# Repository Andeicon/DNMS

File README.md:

# Digital Noice Meter, Particular Matter, Humidity, Air Pressure & Temperature sensor
### based/forked on the great work of Helmut Bitters DNMS (https://github.com/hbitter/DNMS)

This PCB is based on the DNMS-T4.0+NodeMCU Bord of H.Bitters project changed for my own designed 3d Printed case.

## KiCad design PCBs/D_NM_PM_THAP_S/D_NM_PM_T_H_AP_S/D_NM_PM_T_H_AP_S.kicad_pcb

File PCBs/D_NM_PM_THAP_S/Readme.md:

# Digital Noice Meter, Particular Matter, Humidity, Air Pressure & Temperature sensor
## based/forked on the great work of Helmut Bitters DNMS (https://github.com/hbitter/DNMS)

This PCB is based on the DNMS-T4.0+NodeMCU Bord of H.Bitters project changed for my own disgned 3d Printed case.

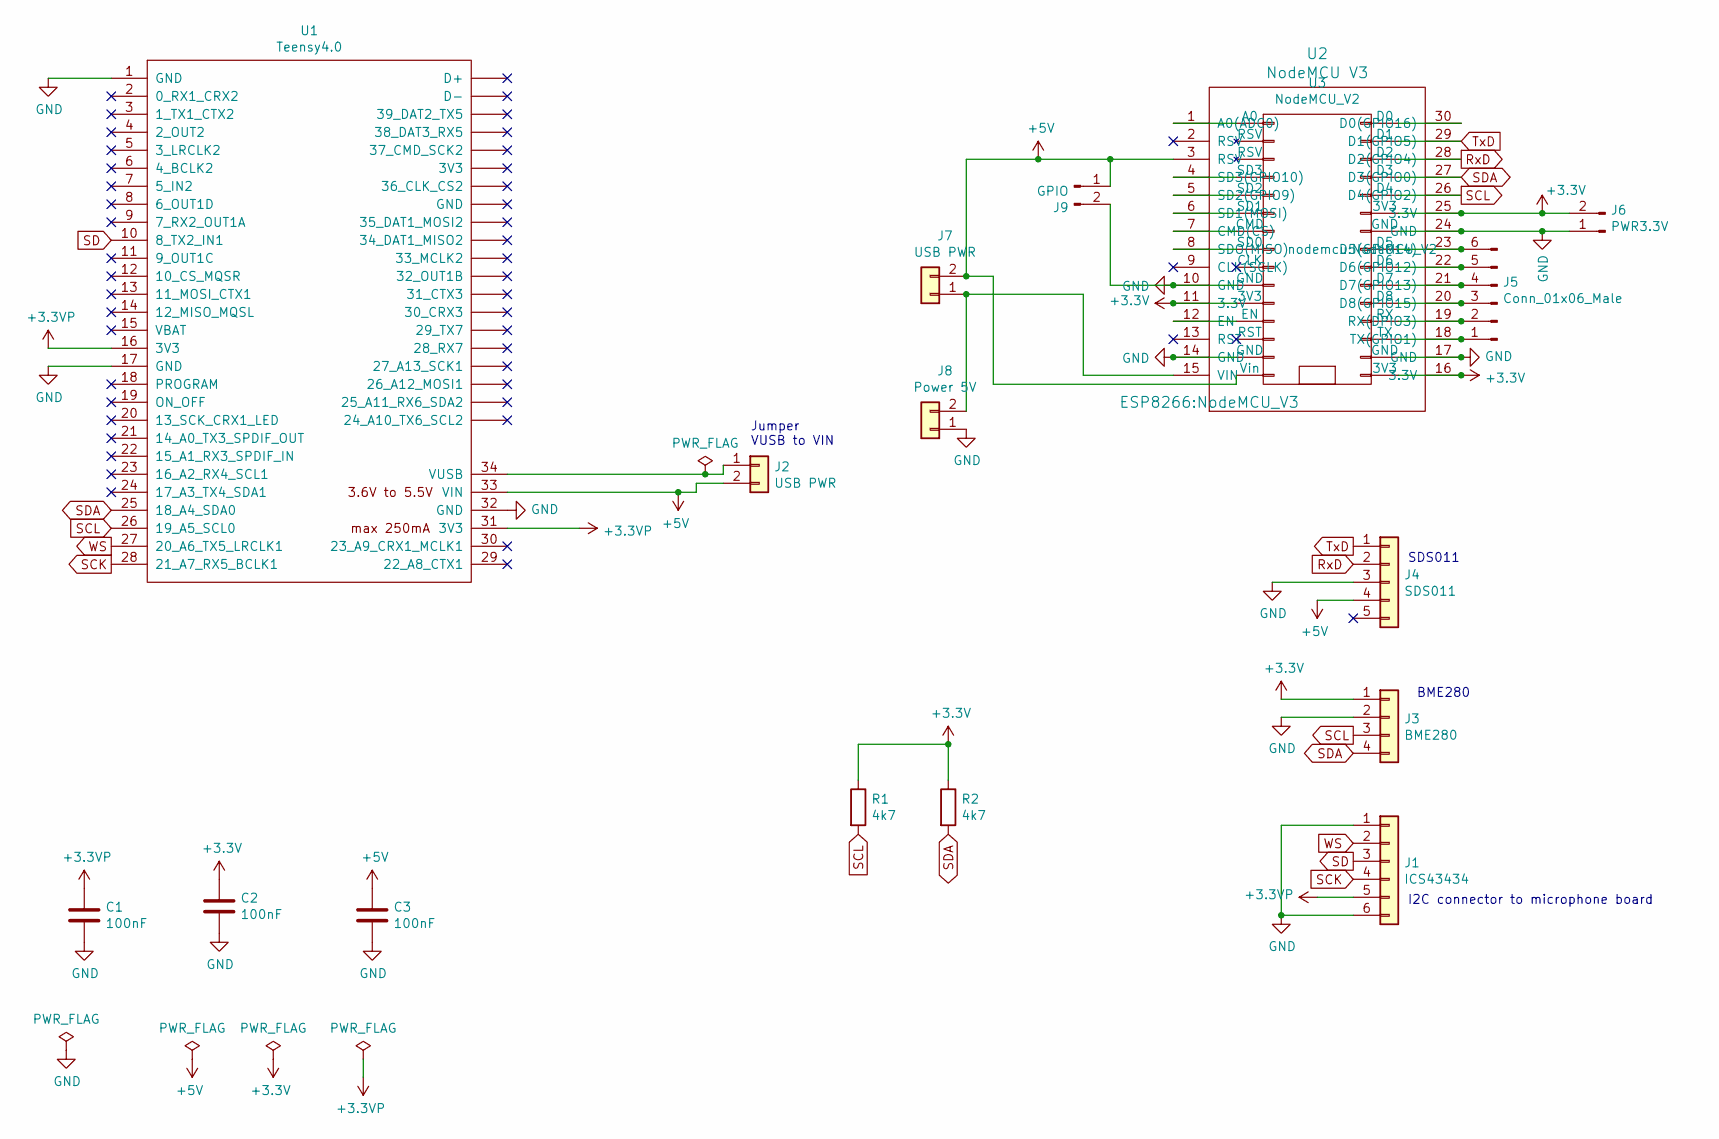
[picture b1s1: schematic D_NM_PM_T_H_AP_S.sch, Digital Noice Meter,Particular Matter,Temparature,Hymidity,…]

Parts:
C1, C2, C3: 100nF; C_Rect_L10.0mm_W5.0mm_P5.00mm_P7.50mm
J1: ICS43434; JST_EH_B6B-EH-A_1x06_P2.50mm_Vertical
J2, J7: USB PWR; PinHeader_1x02_P2.54mm_Vertical
J3: BME280; JST_EH_B4B-EH-A_1x04_P2.50mm_Vertical
J4: SDS011; JST_EH_B4B-EH-A_1x04_P2.50mm_Vertical
J5: Conn_01x06_Male; PinHeader_1x06_P2.54mm_Vertical
J6: PWR3.3V; PinHeader_1x02_P2.54mm_Vertical
J8: Power 5V; JST_EH_B2B-EH-A_1x02_P2.50mm_Vertical
J9: GPIO; PinHeader_1x02_P2.54mm_Vertical
R1, R2: 4k7; R_Axial_DIN0309_L9.0mm_D3.2mm_P12.70mm_Horizontal
U1: Teensy4.0; Teensy40
U2: NodeMCU V3; NodeMCU_V3
U3: NodeMCU_V2

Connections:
+3.3VP: C1.1, J1.5, U1.16 (3V3), U1.31 (3V3)
+3V3: C2.1, J3.1, J6.2, R1.1, R2.1, U2.11 (3.3V), U2.16 (3.3V), U2.25 (3.3V), U3.11 (3V3), U3.16 (3V3), U3.25 (3V3)
+5V: C3.1, J2.2, J4.4, J7.2, J9.1, U1.33 (VIN), U2.3 (RSV), U3.15 (Vin)
GND: C1.2, C2.2, C3.2, J1.1, J1.6, J3.2, J4.3, J6.1, J8.1, J9.2, U1.1 (GND), U1.17 (GND), U1.32 (GND), U2.10 (GND), U2.14 (GND), U2.17 (GND), U2.24 (GND), U3.10 (GND), U3.14 (GND), U3.17 (GND), U3.24 (GND)
unnamed: J2.1, U1.34 (VUSB)
unnamed: J5.1, U2.18 (TX(GPIO1)), U3.18 (TX)
unnamed: J5.2, U2.19 (RX(DPIO3)), U3.19 (RX)
unnamed: J5.3, U2.20 (D8(GPIO15)), U3.20 (D8)
unnamed: J5.4, U2.21 (D7(GPIO13)), U3.21 (D7)
unnamed: J5.5, U2.22 (D6(GPIO12)), U3.22 (D6)
unnamed: J5.6, U2.23 (D5(GPIO14)), U3.23 (D5)
unnamed: J7.1, J8.2, U2.15 (VIN)
unnamed: U2.1 (A0(ADC0)), U3.1 (A0)
unnamed: U2.4 (SD3(GPIO10)), U3.4 (SD3)
unnamed: U2.5 (SD2(GPIO9)), U3.5 (SD2)
unnamed: U2.6 (SD1(MOSI)), U3.6 (SD1)
unnamed: U2.7 (CMD(CS)), U3.7 (CMD)
unnamed: U2.8 (SDO(MISO)), U3.8 (SD0)
unnamed: U2.12 (EN), U3.12 (EN)
unnamed: U2.30 (D0(GPIO16)), U3.30 (D0)
RxD: J4.2, U2.28 (D2(GPIO4)), U3.28 (D2)
SCK: J1.4, U1.28 (21_A7_RX5_BCLK1)
SCL: J3.3, R1.2, U1.26 (19_A5_SCL0), U2.26 (D4(GPIO2)), U3.26 (D4)
SD: J1.3, U1.10 (8_TX2_IN1)
SDA: J3.4, R2.2, U1.25 (18_A4_SDA0), U2.27 (D3(GPIO0)), U3.27 (D3)
TxD: J4.1, U2.29 (D1(GPIO5)), U3.29 (D1)
WS: J1.2, U1.27 (20_A6_TX5_LRCLK1)

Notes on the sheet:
Jumper VUSB to VIN
I2C connector to microphone board
SDS011
BME280

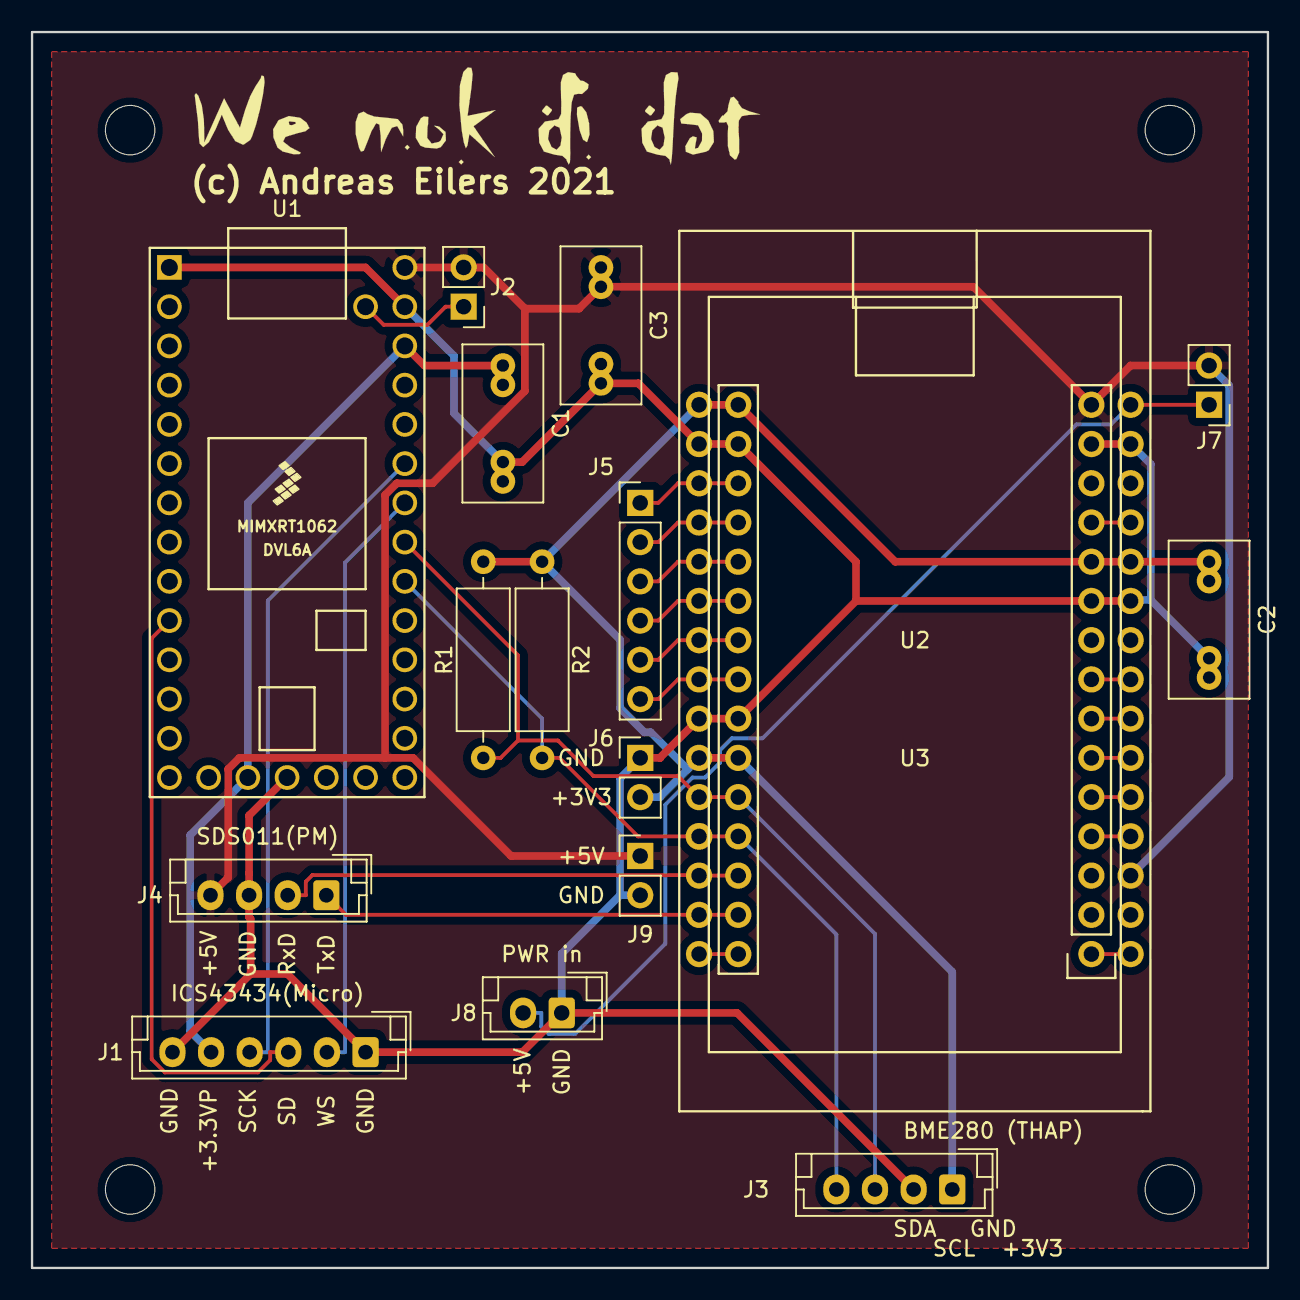
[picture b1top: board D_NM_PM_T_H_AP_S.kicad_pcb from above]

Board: 2 copper layers, 80.0 x 80.0 mm, 21 parts (0 on the bottom side), 27 nets.

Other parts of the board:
REF1, REF2, REF3, REF4: MountingHole_3.2mm_M3

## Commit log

2021-02-03 Basic Changes for my project.
    Deleted files that are not necessary for my project
2021-02-03 Changed Readme
2021-02-03 nothing special
2021-02-15 First shot
